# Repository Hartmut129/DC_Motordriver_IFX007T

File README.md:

# DC_Motordriver_IFX007T
Kicad designfiles for  a high power dc driver based on IFX007T

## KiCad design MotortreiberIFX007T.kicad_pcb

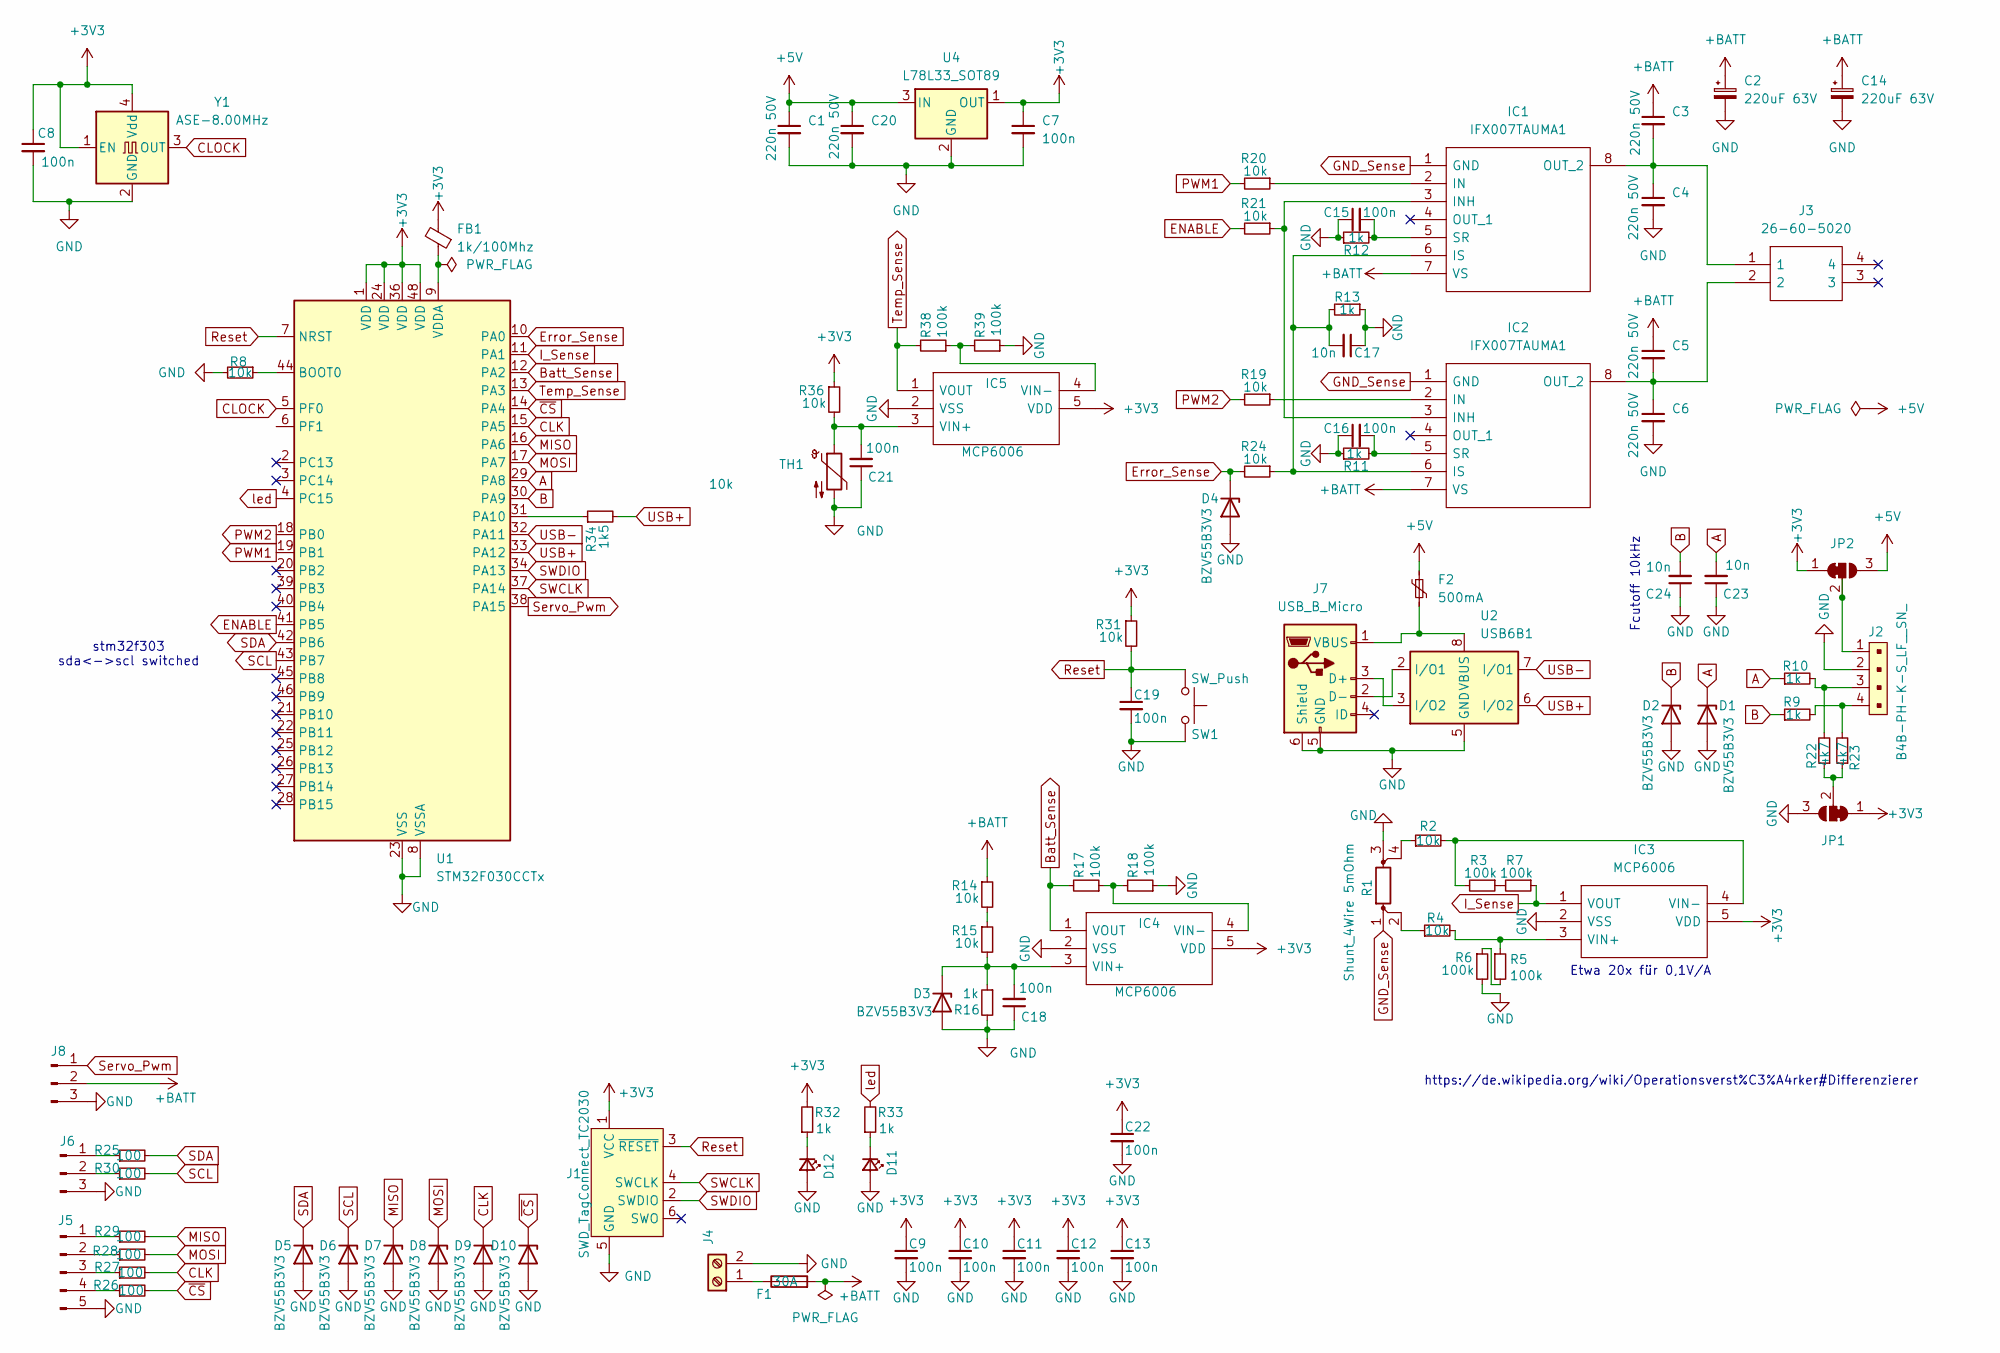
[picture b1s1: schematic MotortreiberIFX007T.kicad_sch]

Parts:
C1, C3, C4, C5, C6, C20: 220n 50V; C_0603_1608Metric
C2, C14: 220uF 63V; CP_Elec_10x10.5
C7, C8, C9, C10, C11, C12, C13, C15, C16, C18, C19, C21, C22: 100n; C_0603_1608Metric
C17, C23, C24: 10n; C_0603_1608Metric
D1, D2, D3, D4, D5, D6, D7, D8, D9, D10: BZV55B3V3; D_MiniMELF
D11, D12: LED_Small; LED_0603_1608Metric
F1: 30A; Fuse_Blade_ATO_directSolder
F2: 500mA; Fuse_1812_4532Metric
FB1: 1k/100Mhz; L_0603_1608Metric
IC1, IC2: IFX007TAUMA1; PG-TO263-7-1; Mouser Part Number 726-IFX007TAUMA1
IC3, IC4, IC5: MCP6006; SOT65P210X110-5N; Manufacturer_Part_Number MCP6006T-E/LT
J1: SWD_TagConnect_TC2030; Tag-Connect_TC2030-IDC-FP_2x03_P1.27mm_Vertical
J2: B4B-PH-K-S_LF__SN_; PinHeader_1x4_P2mm_Drill1mm; MPN B4B-PH-K-S(LF)(SN)
J3: 26-60-5020; XT60PWM; Mouser Part Number 538-26-60-5020
J4: Screw_Terminal_01x02; TerminalBlock_Phoenix_MKDS-1,5-2-5.08_1x02_P5.08mm_Horizont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
J5: Conn_01x05_Pin; JST_XH_B5B-XH-AM_1x05_P2.50mm_Vertical
J6: Conn_01x03_Pin; JST_XH_B3B-XH-AM_1x03_P2.50mm_Vertical
J7: USB_B_Micro; USB_Micro-B_Wuerth_629105150521
J8: Conn_01x03_Pin; PinHeader_1x03_P2.54mm_Vertical
JP1, JP2: SolderJumper_3_Bridged12; SolderJumper-3_P1.3mm_Bridged12_Pad1.0x1.5mm
R1: Shunt_4Wire 5mOhm; pcb_Shunt
R2, R4, R8, R14, R15, R19, R20, R21, R24, R31, R36: 10k; R_0603_1608Metric
R3, R5, R6, R7, R17, R18, R38, R39: 100k; R_0603_1608Metric
R9, R10, R11, R12, R13, R16, R32, R33: 1k; R_0603_1608Metric
R22, R23: 4k7; R_0603_1608Metric
R25, R26, R27, R28, R29, R30: 100; R_0603_1608Metric
R34: 1k5; R_0603_1608Metric
SW1: SW_Push; SW_Push_SPST_NO_Alps_SKRK
TH1: 10k; R_0603_1608Metric
U1: STM32F030CCTx; LQFP-48_7x7mm_P0.5mm
U2: USB6B1; SOIC-8_3.9x4.9mm_P1.27mm
U4: L78L33_SOT89; SOT-89-3
Y1: ASE-8.00MHz; Oscillator_SMD_Abracon_ASE-4Pin_3.2x2.5mm

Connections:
+3V3: C7.1, C8.1, C9.1, C10.1, C11.1, C12.1, C13.1, C22.1, FB1.2, IC3.5 (VDD), IC4.5 (VDD), IC5.5 (VDD), J1.1 (VCC), JP1.1 (A), JP2.1 (A), R31.1, R32.2, R36.1, U1.1 (VDD), U1.24 (VDD), U1.36 (VDD), U1.48 (VDD), U4.1 (OUT), Y1.1 (EN), Y1.4 (Vdd)
+5V: C1.1, C20.1, F2.1, JP2.3 (B), U4.3 (IN)
+BATT: C2.1, C3.1, C5.1, C14.1, F1.2, IC1.7 (VS), IC2.7 (VS), J8.2, R14.1
A: C23.2, D1.1 (K), R10.1, U1.29 (PA8)
B: C24.2, D2.1 (K), R9.1, U1.30 (PA9)
Batt_Sense: IC4.1 (VOUT), R17.2, U1.12 (PA2)
CLK: D9.1 (K), R27.2, U1.15 (PA5)
CLOCK: U1.5 (PF0), Y1.3 (OUT)
ENABLE: R21.2, U1.41 (PB5)
Error_Sense: D4.1 (K), R24.2, U1.10 (PA0)
GND: C1.2, C2.2, C4.2, C6.2, C7.2, C8.2, C9.2, C10.2, C11.2, C12.2, C13.2, C14.2, C15.1, C16.1, C17.1, C18.1, C19.2, C20.2, C21.1, C22.2, C23.1, C24.1, D1.2 (A), D2.2 (A), D3.2 (A), D4.2 (A), D5.2 (A), D6.2 (A), D7.2 (A), D8.2 (A), D9.2 (A), D10.2 (A), D11.2 (A), D12.2 (A), IC3.2 (VSS), IC4.2 (VSS), IC5.2 (VSS), J1.5 (GND), J2.2, J4.2, J5.5, J6.3, J7.5 (GND), J7.6 (Shield), J8.3, JP1.3 (B), R1.3, R6.2, R8.2, R11.1, R12.1, R13.1, R16.2, R18.1, R39.1, SW1.2, TH1.2, U1.8 (VSSA), U1.23 (VSS), U1.35 (VSS), U1.47 (VSS), U2.4 (GND), U2.5 (GND), U4.2 (GND), Y1.2 (GND)
GND_Sense: IC1.1 (GND), IC2.1 (GND), R1.1
I_Sense: IC3.1 (VOUT), R7.1, U1.11 (PA1)
MISO: D7.1 (K), R29.2, U1.16 (PA6)
MOSI: D8.1 (K), R28.2, U1.17 (PA7)
unnamed: C18.2, D3.1 (K), IC4.3 (VIN+), R15.2, R16.1
unnamed: D11.1 (K), R33.1
unnamed: D12.1 (K), R32.1
unnamed: IC1.2 (IN), R20.1
unnamed: IC1.3 (INH), IC2.3 (INH), R21.1
unnamed: C17.2, IC1.6 (IS), IC2.6 (IS), R13.2, R24.1
unnamed: C3.2, C4.1, IC1.8 (OUT_2), J3.1
unnamed: C15.2, IC1.5 (SR), R12.2
unnamed: IC2.2 (IN), R19.1
unnamed: C5.2, C6.1, IC2.8 (OUT_2), J3.2
unnamed: C16.2, IC2.5 (SR), R11.2
unnamed: IC3.3 (VIN+), R4.2, R5.1
unnamed: IC3.4 (VIN-), R2.2, R3.2
unnamed: IC4.4 (VIN-), R17.1, R18.2
unnamed: C21.2, IC5.3 (VIN+), R36.2, TH1.1
unnamed: IC5.4 (VIN-), R38.1, R39.2
unnamed: J2.3, R10.2, R22.2
unnamed: J2.4, R9.2, R23.2
unnamed: F1.1, J4.1
unnamed: J5.1, R29.1
unnamed: J5.2, R28.1
unnamed: J5.3, R27.1
unnamed: J5.4, R26.1
unnamed: J6.1, R25.1
unnamed: J6.2, R30.1
unnamed: J7.3 (D+), U2.3 (I/O2)
unnamed: J7.2 (D-), U2.2 (I/O1)
unnamed: F2.2, J7.1 (VBUS), U2.1 (VBUS), U2.8 (VBUS)
unnamed: JP1.2 (C), R22.1, R23.1
unnamed: J2.1, JP2.2 (C)
unnamed: R1.2, R4.1
unnamed: R1.4, R2.1
unnamed: R3.1, R7.2
unnamed: R5.2, R6.1
unnamed: R14.2, R15.1
unnamed: R8.1, U1.44 (BOOT0)
unnamed: R34.1, U1.31 (PA10)
unnamed: FB1.1, U1.9 (VDDA)
PWM1: R20.2, U1.19 (PB1)
PWM2: R19.2, U1.18 (PB0)
Reset: C19.1, J1.3 (~RESET), R31.2, SW1.1, U1.7 (NRST)
SCL: D6.1 (K), R30.2, U1.43 (PB7)
SDA: D5.1 (K), R25.2, U1.42 (PB6)
SWCLK: J1.4 (SWCLK), U1.37 (PA14)
SWDIO: J1.2 (SWDIO), U1.34 (PA13)
Servo_Pwm: J8.1, U1.38 (PA15)
Temp_Sense: IC5.1 (VOUT), R38.2, U1.13 (PA3)
USB+: R34.2, U1.33 (PA12), U2.6 (I/O2)
USB-: U1.32 (PA11), U2.7 (I/O1)
led: R33.2, U1.4 (PC15)
~CS: D10.1 (K), R26.2, U1.14 (PA4)

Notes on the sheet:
stm32f303 sda<->scl switched
https://de.wikipedia.org/wiki/Operationsverst%C3%A4rker#Differenzierer
Etwa 20x für 0,1V/A
Fcutoff 10kHz

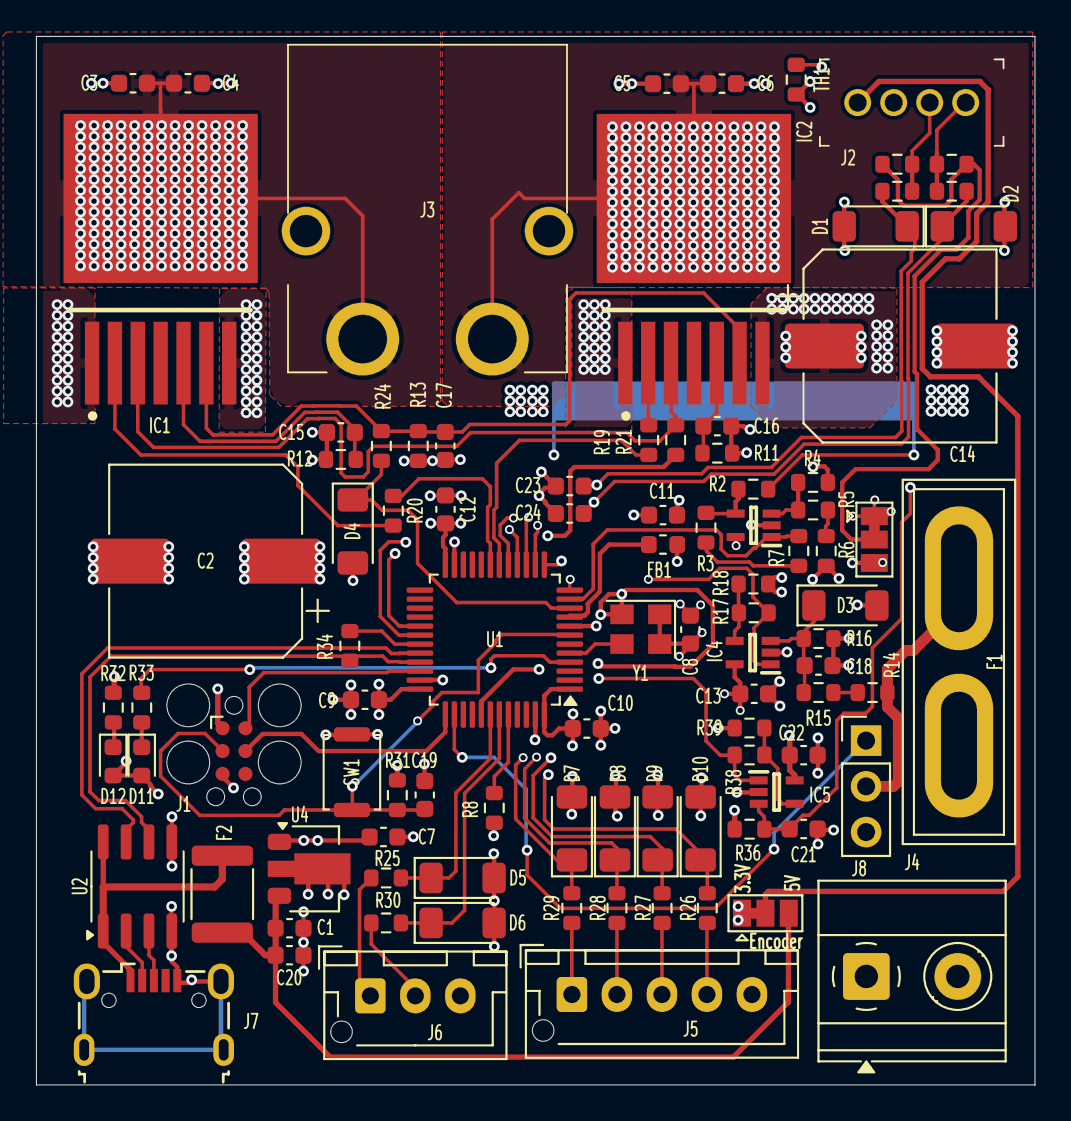
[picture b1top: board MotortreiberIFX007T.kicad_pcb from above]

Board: 4 copper layers, 55.5 x 58.2 mm, 97 parts (1 on the bottom side), 66 nets.
